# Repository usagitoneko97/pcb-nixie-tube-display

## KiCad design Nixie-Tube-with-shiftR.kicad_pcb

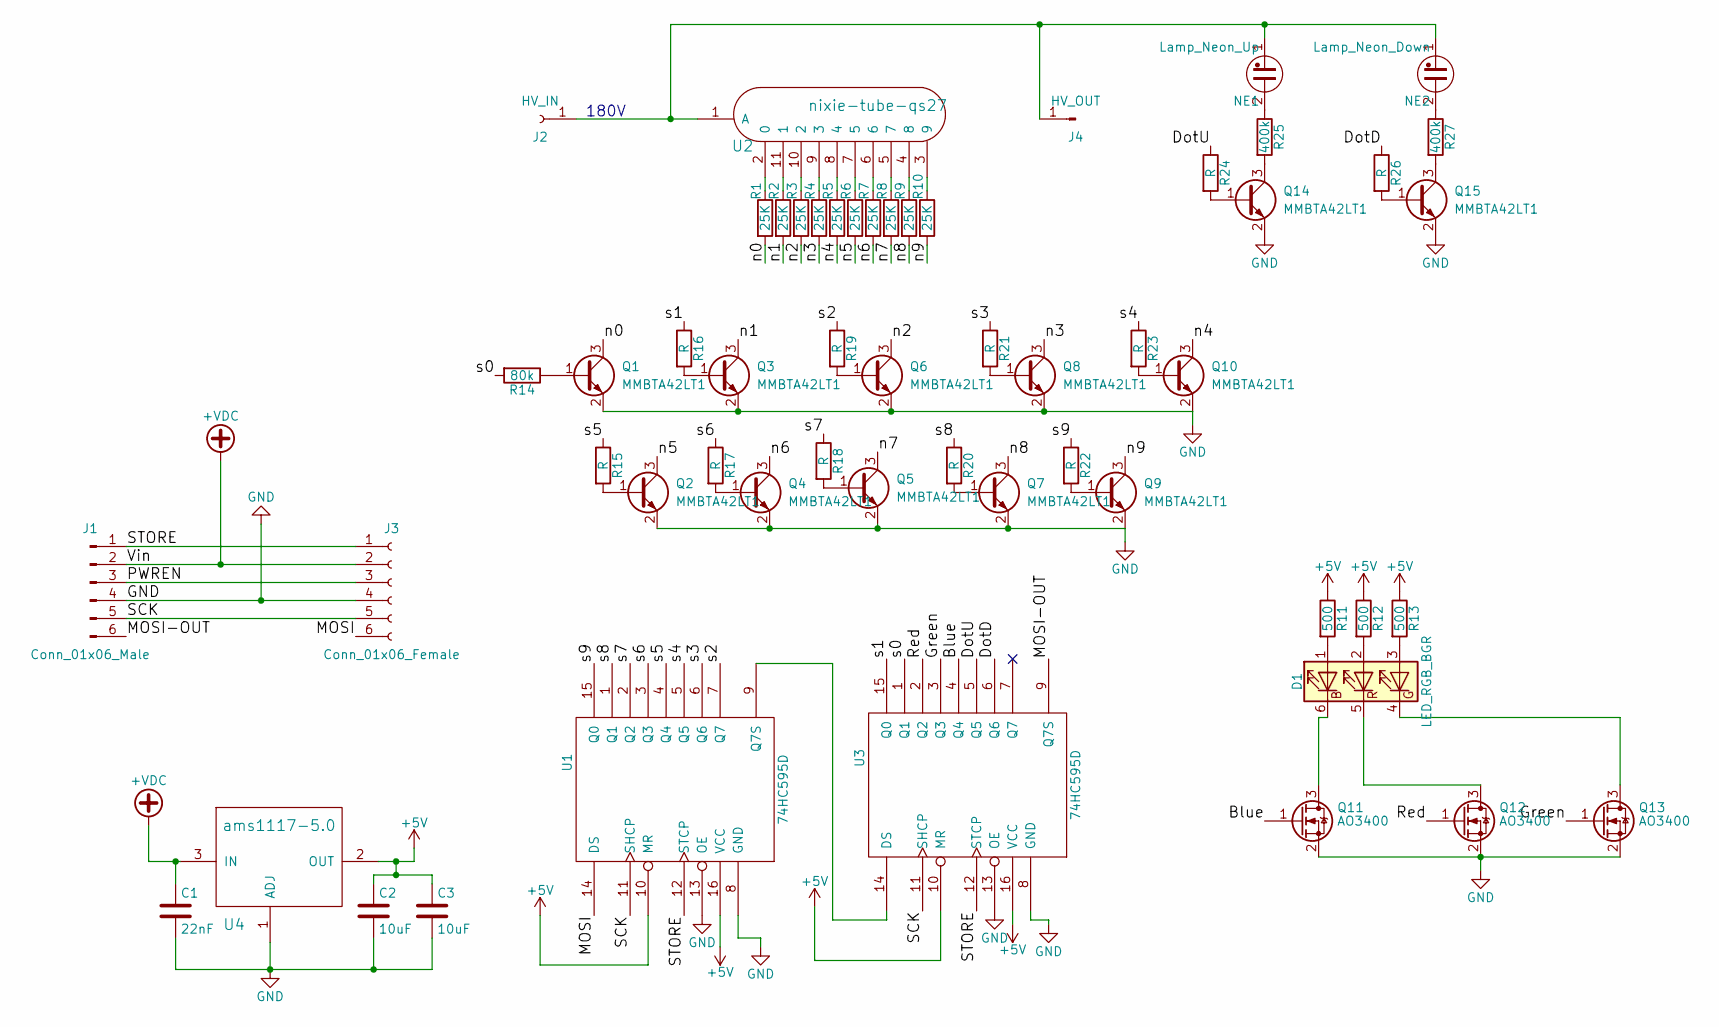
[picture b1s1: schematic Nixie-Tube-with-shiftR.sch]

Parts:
C1: 22nF; C_0603
C2, C3: 10uF; C_0603
D1: LED_RGB_BGR; LED_RGB_5050-6
J1: Conn_01x06_Male; Pin_Header_Angled_1x06_Pitch2.54mm
J2: HV_IN; Socket_Strip_Angled_1x01_Pitch2.54mm_without_silk
J3: Conn_01x06_Female; Socket_Strip_Angled_1x06_Pitch2.54mm_without_silk
J4: HV_OUT; Pin_Header_Angled_1x01_Pitch2.54mm
NE1: Lamp_Neon_Up; neon-tube
NE2: Lamp_Neon_Down; neon-tube
Q1, Q2, Q3, Q4, Q5, Q6, Q7, Q8, Q9, Q10, Q14, Q15: MMBTA42LT1; SOT-23
Q11, Q12, Q13: AO3400; SOT-23
R1, R2, R3, R4, R5, R6, R7, R8, R9, R10: 25K; R_0603
R11, R12, R13: 500; R_0603
R14: 80k; R_0603
R15, R16, R17, R18, R19, R20, R21, R22, R23, R24, R26: R; R_0603
R25, R27: 400k; R_0603
U1, U3: 74HC595D; SO16
U2: nixie-tube-qs27; qs27-1
U4: ams1117-5.0; SOT-223-3Lead_TabPin2

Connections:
+5V: C2.1, C3.1, R11.1, R12.1, R13.1, U1.10 (MR), U1.16 (VCC), U3.10 (MR), U3.16 (VCC), U4.2 (OUT)
+VDC: C1.1, J1.2, J3.2, U4.3 (IN)
/Blue: Q11.1 (G), U3.4 (Q4)
/DotD: R26.1, U3.6 (Q6)
/DotU: R24.1, U3.5 (Q5)
/Green: Q13.1 (G), U3.3 (Q3)
/MOSI: J3.6, U1.14 (DS)
/MOSI-OUT: J1.6, U3.9 (Q7S)
/PWREN: J1.3, J3.3
/Red: Q12.1 (G), U3.2 (Q2)
/SCK: J1.5, J3.5, U1.11 (SHCP), U3.11 (SHCP)
/STORE: J1.1, J3.1, U1.12 (STCP), U3.12 (STCP)
/n0: Q1.3 (C), R1.2
/n1: Q3.3 (C), R2.2
/n2: Q6.3 (C), R3.2
/n3: Q8.3 (C), R4.2
/n4: Q10.3 (C), R5.2
/n5: Q2.3 (C), R6.2
/n6: Q4.3 (C), R7.2
/n7: Q5.3 (C), R8.2
/n8: Q7.3 (C), R9.2
/n9: Q9.3 (C), R10.2
/s0: R14.2, U3.1 (Q1)
/s1: R16.1, U3.15 (Q0)
/s2: R19.1, U1.7 (Q7)
/s3: R21.1, U1.6 (Q6)
/s4: R23.1, U1.5 (Q5)
/s5: R15.1, U1.4 (Q4)
/s6: R17.1, U1.3 (Q3)
/s7: R18.1, U1.2 (Q2)
/s8: R20.1, U1.1 (Q1)
/s9: R22.1, U1.15 (Q0)
GND: C1.2, C2.2, C3.2, J1.4, J3.4, Q1.2 (E), Q2.2 (E), Q3.2 (E), Q4.2 (E), Q5.2 (E), Q6.2 (E), Q7.2 (E), Q8.2 (E), Q9.2 (E), Q10.2 (E), Q11.2 (S), Q12.2 (S), Q13.2 (S), Q14.2 (E), Q15.2 (E), U1.8 (GND), U1.13 (OE), U3.8 (GND), U3.13 (OE), U4.1 (ADJ)
unnamed: D1.1 (RA), R11.2
unnamed: D1.2 (GA), R12.2
unnamed: D1.3 (BA), R13.2
unnamed: D1.4 (BK), Q13.3 (D)
unnamed: D1.5 (GK), Q12.3 (D)
unnamed: D1.6 (RK), Q11.3 (D)
unnamed: J2.1, J4.1, NE1.1, NE2.1, U2.1 (A)
unnamed: NE1.2, R25.1
unnamed: NE2.2, R27.1
unnamed: Q1.1 (B), R14.1
unnamed: Q2.1 (B), R15.2
unnamed: Q3.1 (B), R16.2
unnamed: Q4.1 (B), R17.2
unnamed: Q5.1 (B), R18.2
unnamed: Q6.1 (B), R19.2
unnamed: Q7.1 (B), R20.2
unnamed: Q8.1 (B), R21.2
unnamed: Q9.1 (B), R22.2
unnamed: Q10.1 (B), R23.2
unnamed: Q14.1 (B), R24.2
unnamed: Q14.3 (C), R25.2
unnamed: Q15.1 (B), R26.2
unnamed: Q15.3 (C), R27.2
unnamed: R1.1, U2.2 (0)
unnamed: R2.1, U2.11 (1)
unnamed: R3.1, U2.10 (2)
unnamed: R4.1, U2.9 (3)
unnamed: R5.1, U2.8 (4)
unnamed: R6.1, U2.7 (5)
unnamed: R7.1, U2.6
unnamed: R8.1, U2.5 (7)
unnamed: R9.1, U2.4 (8)
unnamed: R10.1, U2.3 (9)
unnamed: U1.9 (Q7S), U3.14 (DS)

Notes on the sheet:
180V

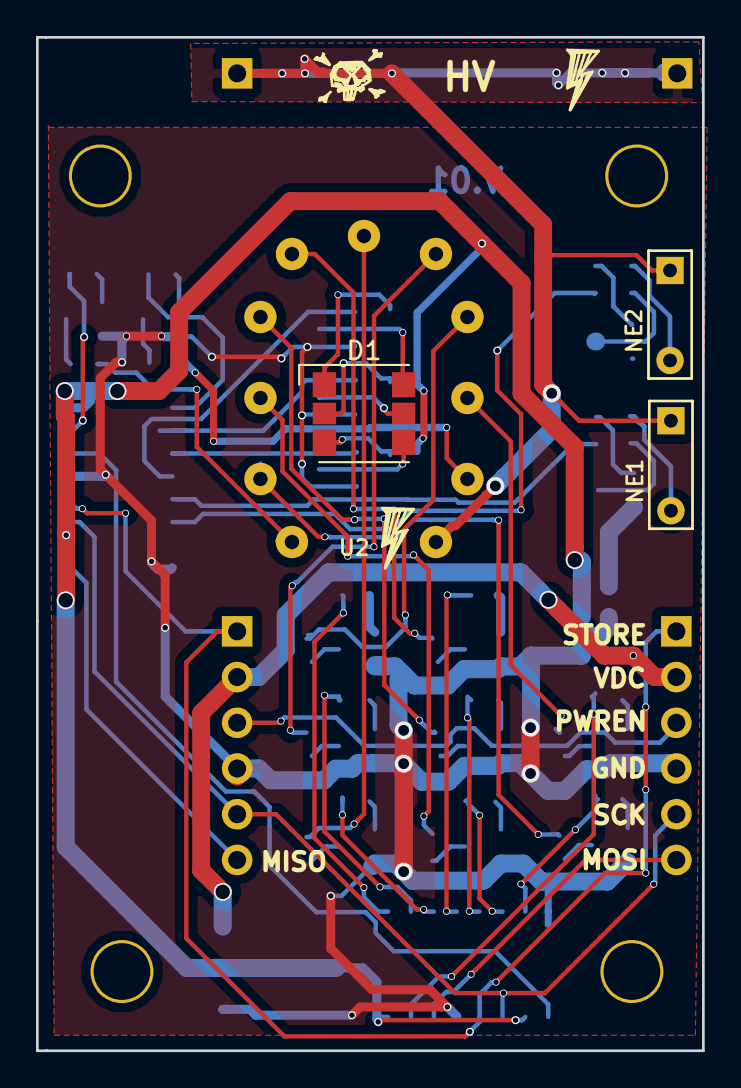
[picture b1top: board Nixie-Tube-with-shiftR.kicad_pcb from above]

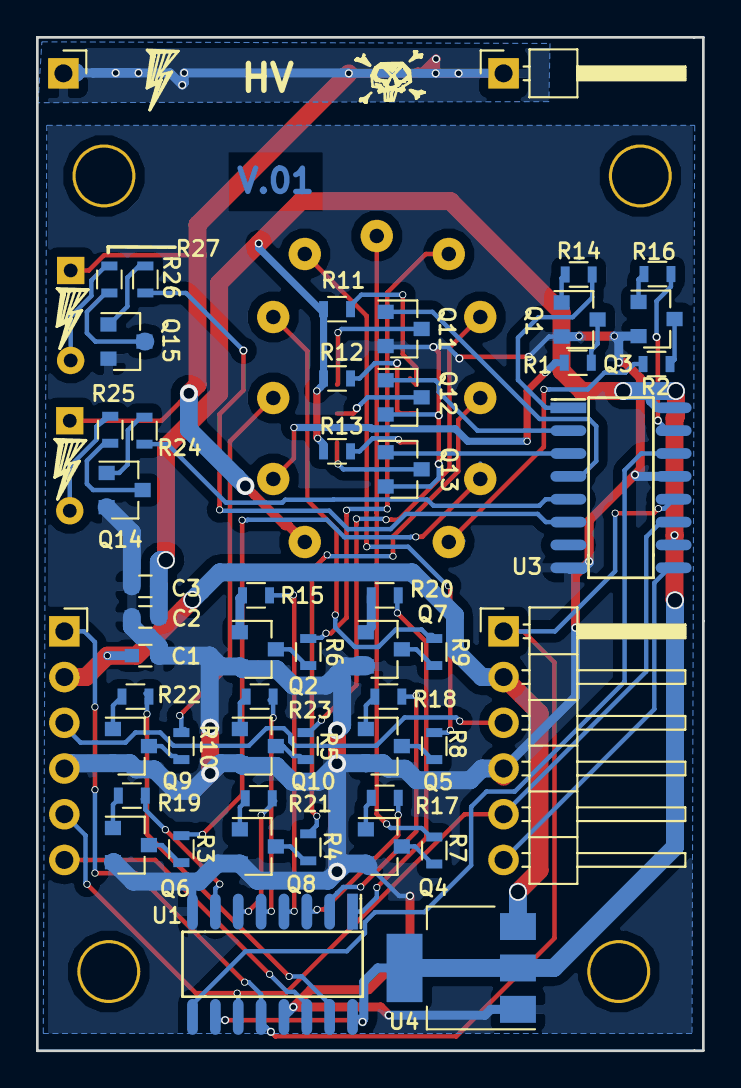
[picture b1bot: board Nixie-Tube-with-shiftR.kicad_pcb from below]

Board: 2 copper layers, 37.0 x 56.3 mm, 63 parts (56 on the bottom side), 67 nets.

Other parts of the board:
Z?: lightning
Z?#2, Z?#3, Z?#4, Z?#7: lightning
Z?#5, Z?#6: skull

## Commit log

2017-10-11 created nixie tube schematic
2017-10-12 finalize schematic, added so16 footprint
2017-10-12 associate all footprints, components are outside of board
2017-10-12 change ldo to 5V
2017-10-13 arrangement v1 (higher board size)
2017-10-13 first attempt to route
2017-10-13 rearrange resistor to vertical
2017-10-13 routed number 0-9
2017-10-13 route all components but ground
2017-10-13 0 unconnected
2017-10-13 fixed pin headers position
2017-10-14 placed all the component
2017-10-15 added dimension in text on eco1user
2017-10-15 routed s0-s9
2017-10-15 new alignment idea
2017-10-15 place group(cap and R) parallel to the R, unite the track to nixie to 1 side
2017-10-16 routed all but ground
2017-10-17 completed routing, swap pin headers
2017-10-17 mosi line bugged
2017-10-17 finalize board layout and tracks
2017-10-17 modify board layout dimension text
2017-10-18 fix track being too near to border line
2017-10-18 modify 9V gnd tracks bigger
2017-10-20 added OE to the pins
2017-10-20 fixed issues on the connectivity on layout
2017-10-20 placement of resistor
2017-10-21 change the sequence of s0-s9
2017-10-22 move shift reg to bottom
2017-10-23 finalized position, briefly routed
2017-10-24 align the components
2017-10-29 finished routed all tracks
2017-10-30 fixed pin headers placement not the same with power supply
2017-11-07 extend board in y dir for placing the 2 headers bottom
2017-11-09 adjust board layout to fit with 7mm pin
2017-11-13 adjusted dimension on the 4 m3 holes
2017-11-14 added 4 m3 holes
2017-11-14 widen tracks width at HV
2017-11-14 move all components to bottom, preparing to reroute :(
2017-11-14 finished routed all tracks :), references need to place, triple check components and footprint from taobao
2017-11-14 placed all references accordingly
2017-11-15 change m3 pins to no net
2017-11-15 routed qs27-1 on the main pcbnew
2017-11-15 fixed tracks too near to edge
2017-11-15 changed AO3400 pin position (2 board)
2017-11-15 rename file according to the project
    nixie-tube-display-with-shiftR is qs27 while roundxx is qs30
2017-11-16 remove silkscreen on female pins, re routed some of the tracks
2017-11-16 fixed some badly routed tracks
2017-11-16 finalized every component and generated gerber file
2017-11-17 finalized tracks and added symbols
2017-11-17 finalized everything and ready to send out
2017-11-18 fixed various bugs
    RGB led not connected properly to the mosfet
    AO3400 pin orientation is not same with datasheet
    move silkscreen away on neon footprint
2017-11-18 added few things
    lightning symbol on neon and around nixie tube
    via stiching
2017-11-19 fixed 2 of the mmbta42 transistor pin number errors
2017-11-19 fixed ams1117 pin numbering errors
2017-11-21 nixie's legs pin assignment needs to be change
2017-11-21 straighten some tracks
2017-11-21 routed all tracks to fixed pin numbering on nixie tubes
2017-11-22 checked all components, adjusted tracks
